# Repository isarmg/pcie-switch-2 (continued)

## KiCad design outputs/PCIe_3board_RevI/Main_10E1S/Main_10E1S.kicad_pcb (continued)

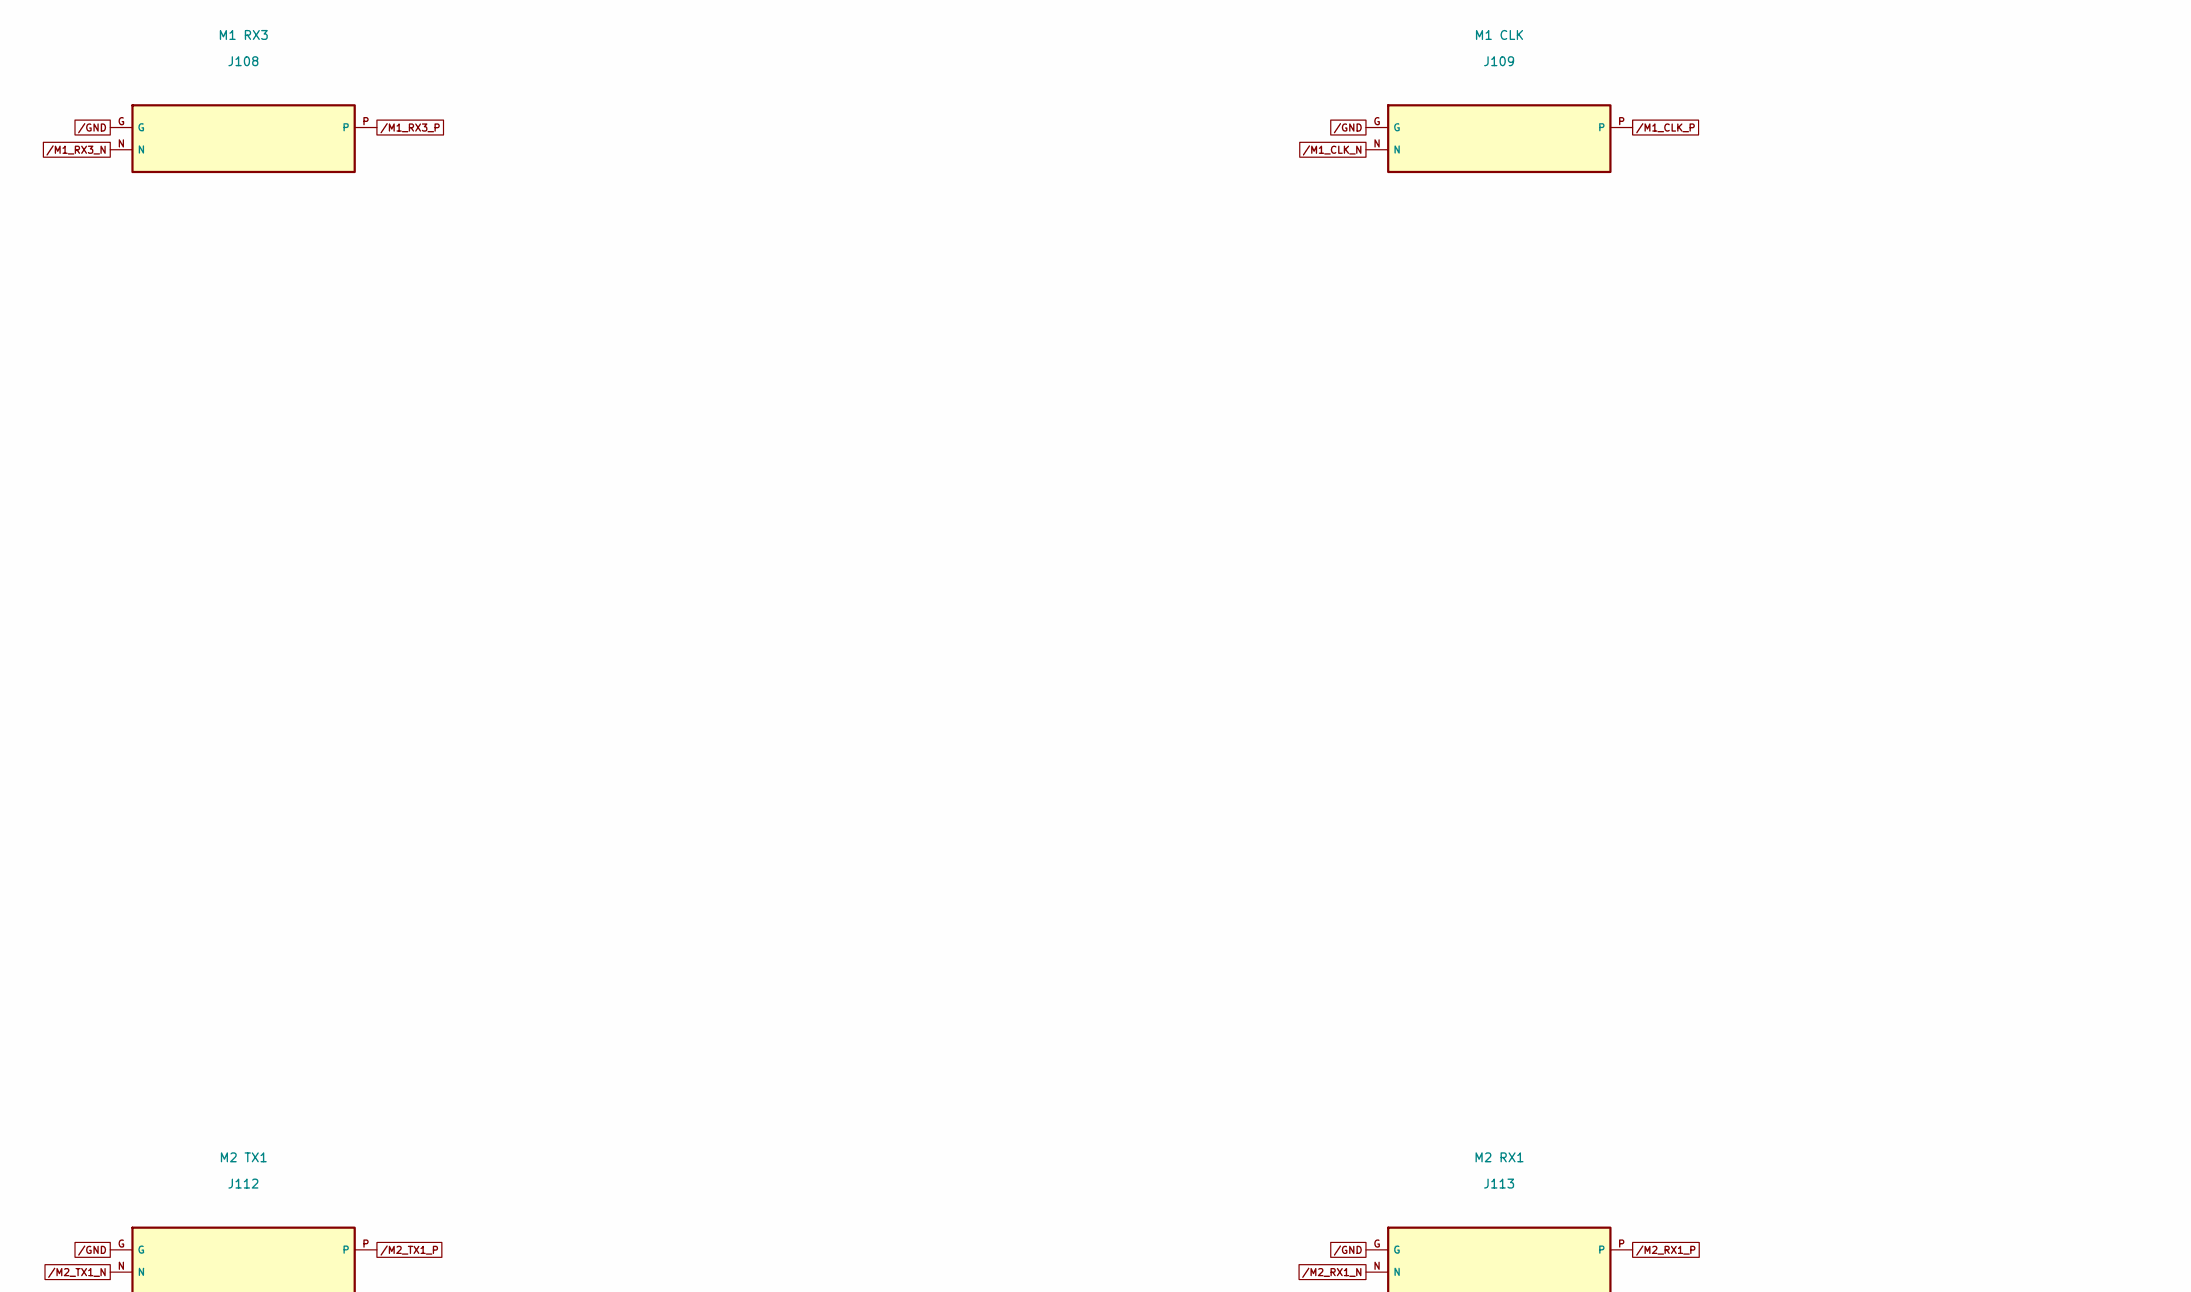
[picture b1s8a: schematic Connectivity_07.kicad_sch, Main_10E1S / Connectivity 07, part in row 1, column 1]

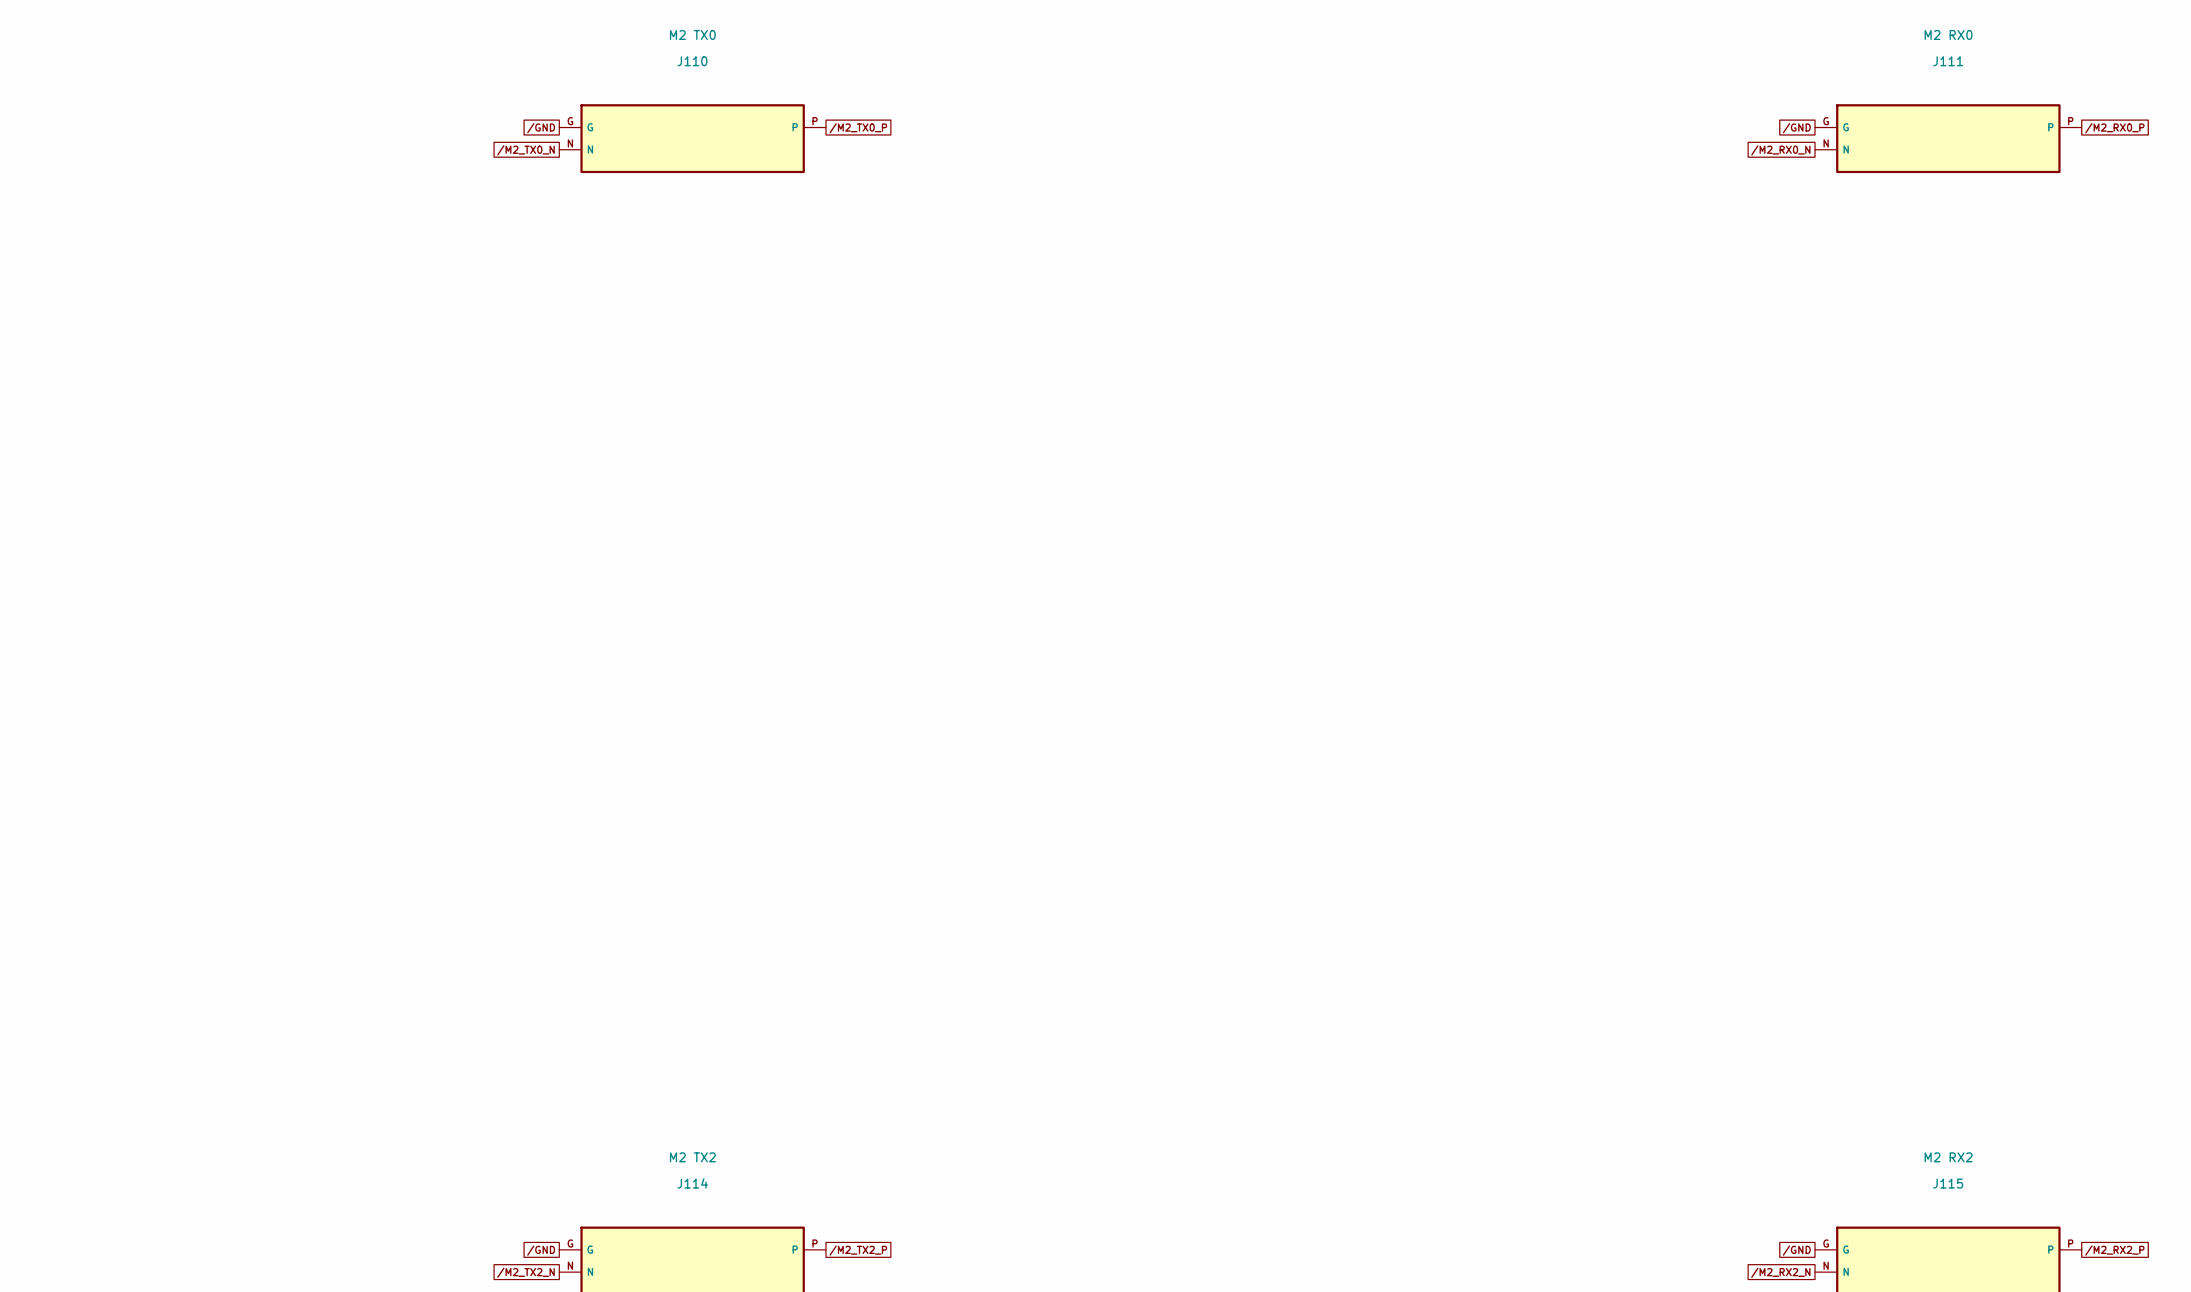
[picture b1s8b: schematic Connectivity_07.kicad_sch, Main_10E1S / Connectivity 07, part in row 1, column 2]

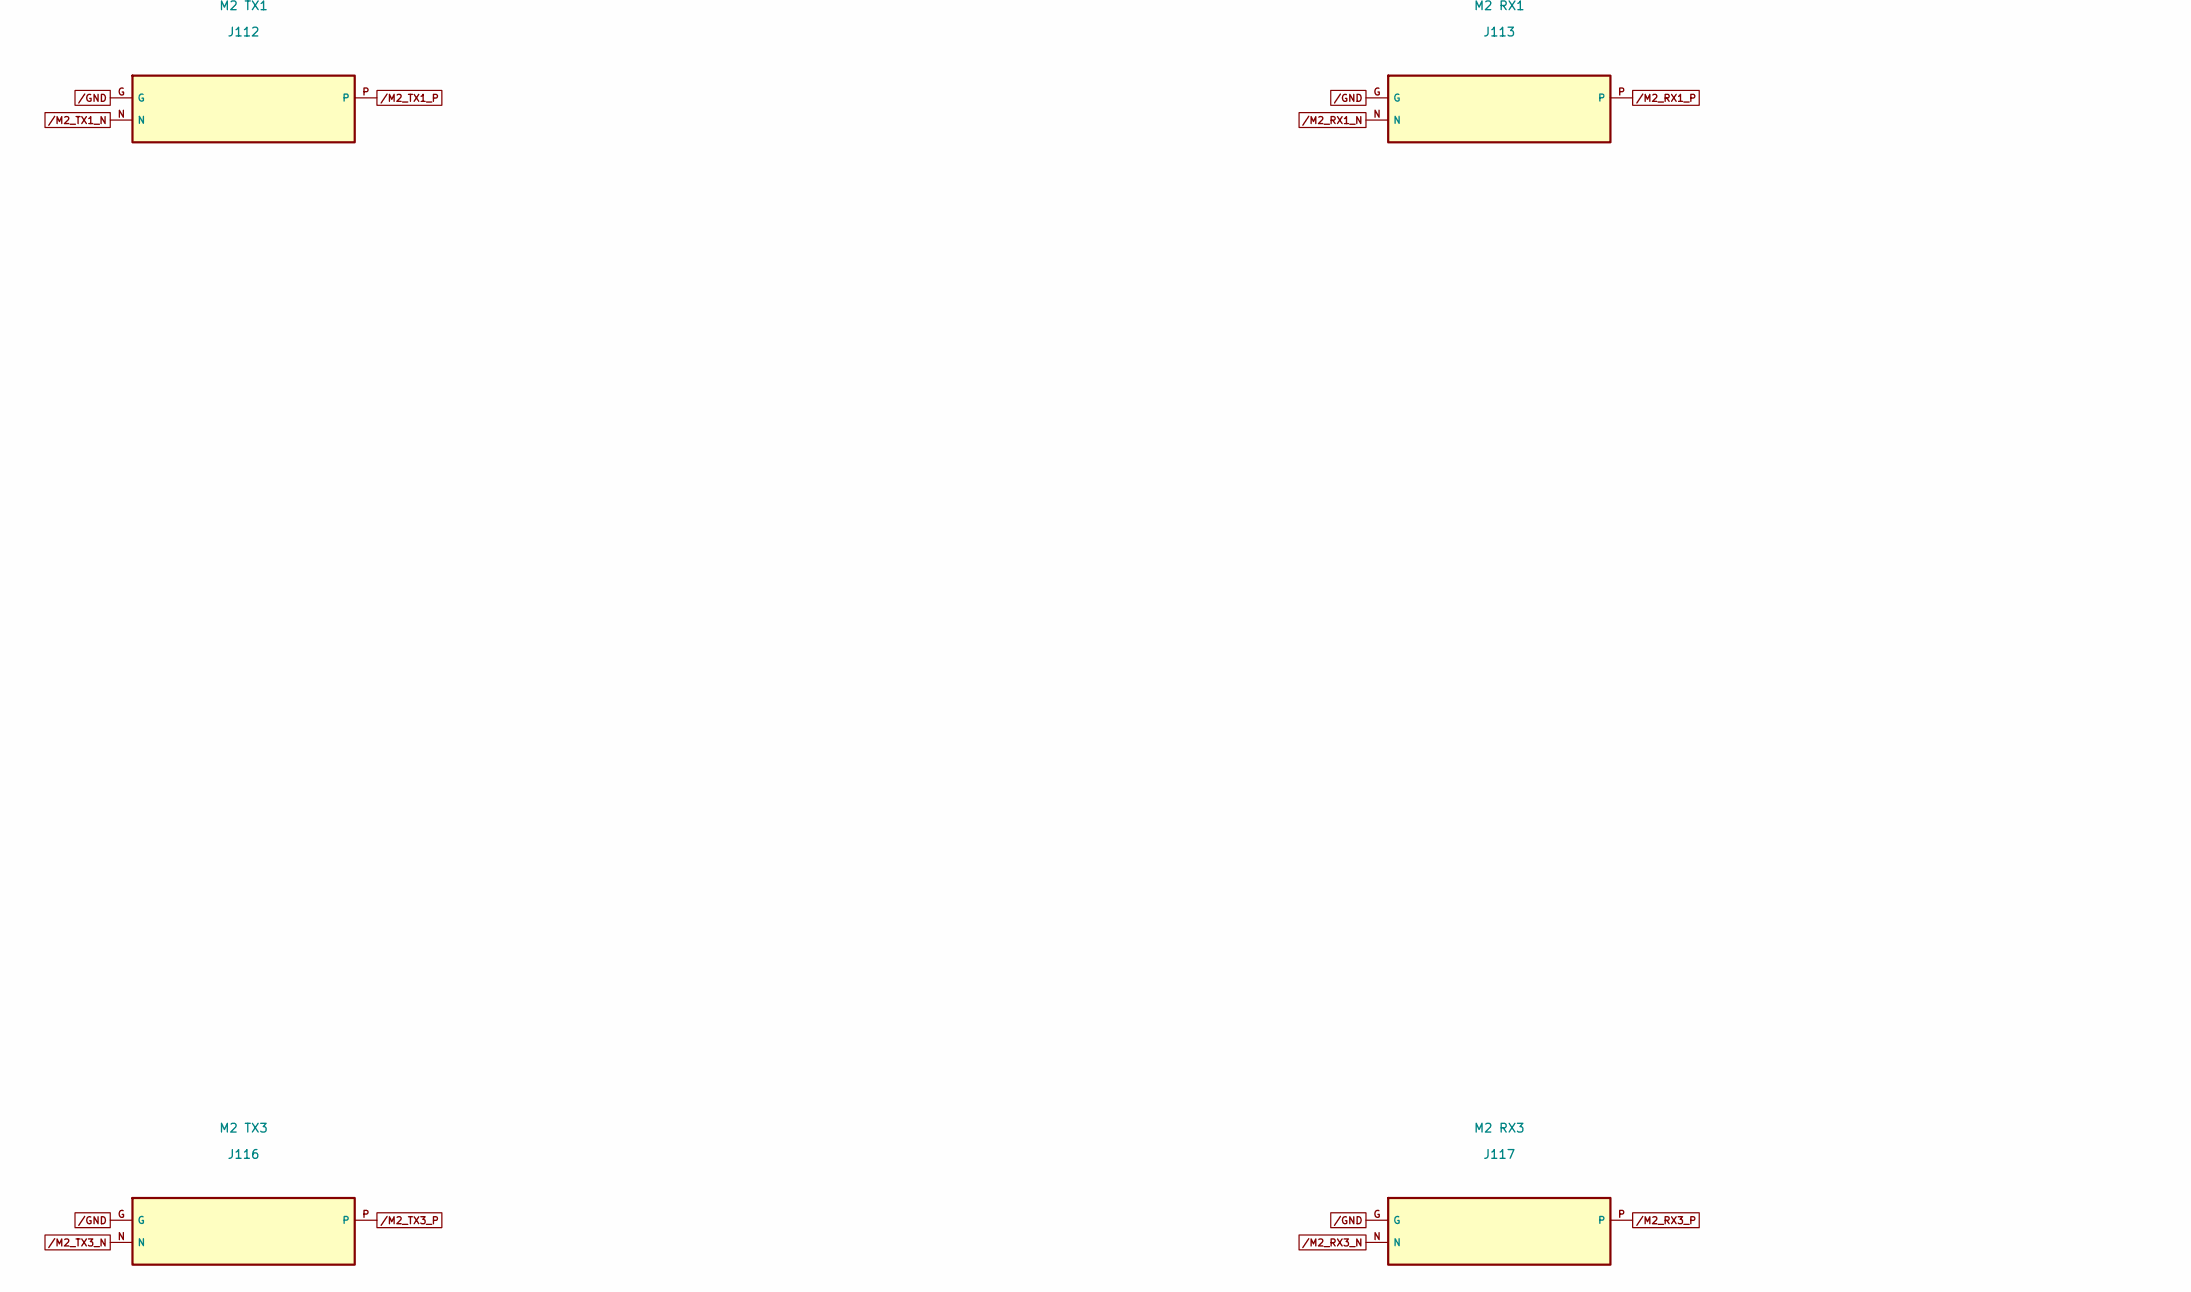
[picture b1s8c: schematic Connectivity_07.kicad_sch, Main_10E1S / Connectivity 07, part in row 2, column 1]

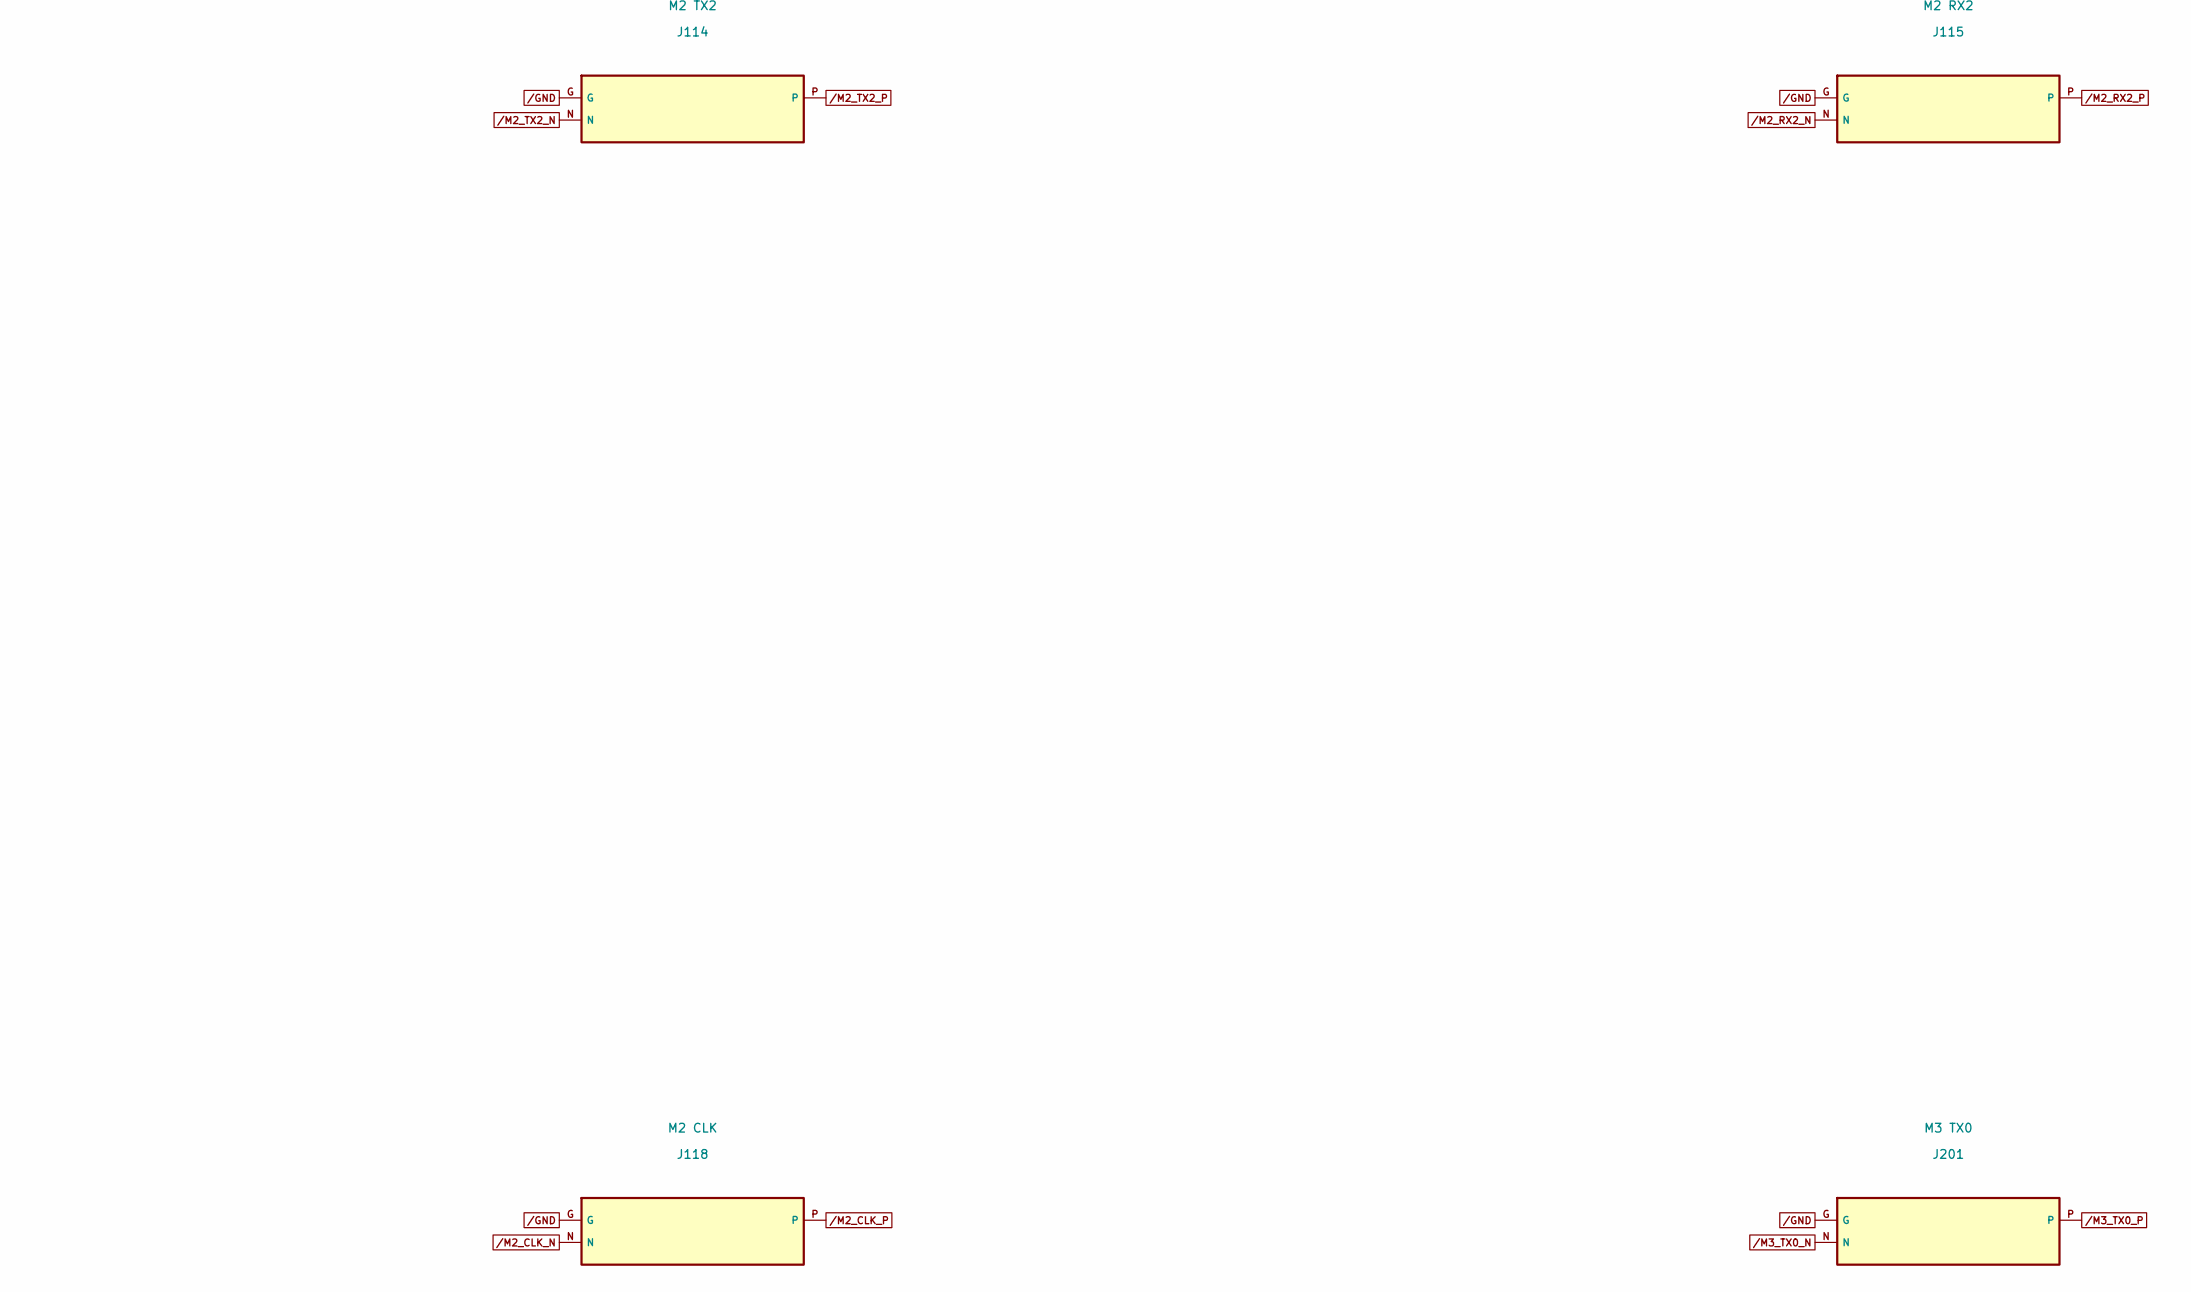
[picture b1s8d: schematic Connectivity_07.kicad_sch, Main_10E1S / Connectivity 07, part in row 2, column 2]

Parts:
J108: M1 RX3; Twinax_85R_Solder_DRAFT
J109: M1 CLK; Twinax_85R_Solder_DRAFT
J110: M2 TX0; Twinax_85R_Solder_DRAFT
J111: M2 RX0; Twinax_85R_Solder_DRAFT
J112: M2 TX1; Twinax_85R_Solder_DRAFT
J113: M2 RX1; Twinax_85R_Solder_DRAFT
J114: M2 TX2; Twinax_85R_Solder_DRAFT
J115: M2 RX2; Twinax_85R_Solder_DRAFT
J116: M2 TX3; Twinax_85R_Solder_DRAFT
J117: M2 RX3; Twinax_85R_Solder_DRAFT
J118: M2 CLK; Twinax_85R_Solder_DRAFT
J201: M3 TX0; Twinax_85R_Solder_DRAFT

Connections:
/GND: J108.G, J109.G, J110.G, J111.G, J112.G, J113.G, J114.G, J115.G, J116.G, J117.G, J118.G, J201.G; also elsewhere on the board
/M1_CLK_N: J109.N; also elsewhere on the board
/M1_CLK_P: J109.P; also elsewhere on the board
/M1_RX3_N: J108.N; also elsewhere on the board
/M1_RX3_P: J108.P; also elsewhere on the board
/M2_CLK_N: J118.N; also elsewhere on the board
/M2_CLK_P: J118.P; also elsewhere on the board
/M2_RX0_N: J111.N; also elsewhere on the board
/M2_RX0_P: J111.P; also elsewhere on the board
/M2_RX1_N: J113.N; also elsewhere on the board
/M2_RX1_P: J113.P; also elsewhere on the board
/M2_RX2_N: J115.N; also elsewhere on the board
/M2_RX2_P: J115.P; also elsewhere on the board
/M2_RX3_N: J117.N; also elsewhere on the board
/M2_RX3_P: J117.P; also elsewhere on the board
/M2_TX0_N: J110.N; also elsewhere on the board
/M2_TX0_P: J110.P; also elsewhere on the board
/M2_TX1_N: J112.N; also elsewhere on the board
/M2_TX1_P: J112.P; also elsewhere on the board
/M2_TX2_N: J114.N; also elsewhere on the board
/M2_TX2_P: J114.P; also elsewhere on the board
/M2_TX3_N: J116.N; also elsewhere on the board
/M2_TX3_P: J116.P; also elsewhere on the board
/M3_TX0_N: J201.N; also elsewhere on the board
/M3_TX0_P: J201.P; also elsewhere on the board

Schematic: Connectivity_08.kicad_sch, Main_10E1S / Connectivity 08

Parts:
J202: M3 RX0; Twinax_85R_Solder_DRAFT
J203: M3 TX1; Twinax_85R_Solder_DRAFT
J204: M3 RX1; Twinax_85R_Solder_DRAFT
J205: M3 TX2; Twinax_85R_Solder_DRAFT
J206: M3 RX2; Twinax_85R_Solder_DRAFT
J207: M3 TX3; Twinax_85R_Solder_DRAFT
J208: M3 RX3; Twinax_85R_Solder_DRAFT
J209: M3 CLK; Twinax_85R_Solder_DRAFT
J210: UP TX0; Twinax_85R_Solder_DRAFT
J211: UP RX0; Twinax_85R_Solder_DRAFT
J212: UP TX1; Twinax_85R_Solder_DRAFT
J213: UP RX1; Twinax_85R_Solder_DRAFT

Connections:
/GND: J202.G, J203.G, J204.G, J205.G, J206.G, J207.G, J208.G, J209.G, J210.G, J211.G, J212.G, J213.G; also elsewhere on the board
/M3_CLK_N: J209.N; also elsewhere on the board
/M3_CLK_P: J209.P; also elsewhere on the board
/M3_RX0_N: J202.N; also elsewhere on the board
/M3_RX0_P: J202.P; also elsewhere on the board
/M3_RX1_N: J204.N; also elsewhere on the board
/M3_RX1_P: J204.P; also elsewhere on the board
/M3_RX2_N: J206.N; also elsewhere on the board
/M3_RX2_P: J206.P; also elsewhere on the board
/M3_RX3_N: J208.N; also elsewhere on the board
/M3_RX3_P: J208.P; also elsewhere on the board
/M3_TX1_N: J203.N; also elsewhere on the board
/M3_TX1_P: J203.P; also elsewhere on the board
/M3_TX2_N: J205.N; also elsewhere on the board
/M3_TX2_P: J205.P; also elsewhere on the board
/M3_TX3_N: J207.N; also elsewhere on the board
/M3_TX3_P: J207.P; also elsewhere on the board
/UP_RX0_N: J211.N; also elsewhere on the board
/UP_RX0_P: J211.P; also elsewhere on the board
/UP_RX1_N: J213.N; also elsewhere on the board
/UP_RX1_P: J213.P; also elsewhere on the board
/UP_TX0_N: J210.N; also elsewhere on the board
/UP_TX0_P: J210.P; also elsewhere on the board
/UP_TX1_N: J212.N; also elsewhere on the board
/UP_TX1_P: J212.P; also elsewhere on the board

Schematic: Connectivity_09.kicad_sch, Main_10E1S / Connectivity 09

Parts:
J214: UP TX2; Twinax_85R_Solder_DRAFT
J215: UP RX2; Twinax_85R_Solder_DRAFT
J216: UP TX3; Twinax_85R_Solder_DRAFT
J217: UP RX3; Twinax_85R_Solder_DRAFT
J218: UP CLK; Twinax_85R_Solder_DRAFT
J301, J302: 12V protected / GND; Wire_12V_GND_3A
J303: L control / custom; Control_8_Wire
J304: R control / custom; Control_8_Wire
L31: 2.2uH; L_Coilcraft_XAL4020-XXX
R101: 76.1k; R_0402_1005Metric
R102: 10k; R_0402_1005Metric

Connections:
/BUCK_SW: L31.1; also elsewhere on the board
/CABLE12_L: J301.1; also elsewhere on the board
/CABLE12_R: J302.1; also elsewhere on the board
/GND: J214.G, J215.G, J216.G, J217.G, J218.G, J301.2, J302.2, J303.7, J303.8, J304.7, J304.8, R102.2; also elsewhere on the board
/M1_CLKREQ: J303.2; also elsewhere on the board
/M1_PERST: J303.1; also elsewhere on the board
/M1_WAKE: J303.3; also elsewhere on the board
/M2_CLKREQ: J303.5; also elsewhere on the board
/M2_PERST: J303.4; also elsewhere on the board
/M2_WAKE: J303.6; also elsewhere on the board
/M3_CLKREQ: J304.2; also elsewhere on the board
/M3_PERST: J304.1; also elsewhere on the board
/M3_WAKE: J304.3; also elsewhere on the board
/P3V3_AUX: L31.2; also elsewhere on the board
/S01_PWR_UV: R101.2, R102.1; also elsewhere on the board
/UP_CLKREQ: J304.5; also elsewhere on the board
/UP_CLK_N: J218.N; also elsewhere on the board
/UP_CLK_P: J218.P; also elsewhere on the board
/UP_PERST: J304.4; also elsewhere on the board
/UP_RX2_N: J215.N; also elsewhere on the board
/UP_RX2_P: J215.P; also elsewhere on the board
/UP_RX3_N: J217.N; also elsewhere on the board
/UP_RX3_P: J217.P; also elsewhere on the board
/UP_TX2_N: J214.N; also elsewhere on the board
/UP_TX2_P: J214.P; also elsewhere on the board
/UP_TX3_N: J216.N; also elsewhere on the board
/UP_TX3_P: J216.P; also elsewhere on the board
/UP_WAKE: J304.6; also elsewhere on the board
/VBANK_A: R101.1; also elsewhere on the board

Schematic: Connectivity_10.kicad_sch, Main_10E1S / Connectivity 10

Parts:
R103, R108, R113: 102k; R_0402_1005Metric
R104, R107, R109, R112, R114: 10k; R_0402_1005Metric
R105, R110: 1.10k; R_0402_1005Metric
R106, R111: 76.1k; R_0402_1005Metric

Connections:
/GND: R104.2, R105.2, R107.2, R109.2, R110.2, R112.2, R114.2; also elsewhere on the board
/S01_PWR_ILM: R105.1; also elsewhere on the board
/S01_PWR_OV: R103.2, R104.1; also elsewhere on the board
/S02_PWR_ILM: R110.1; also elsewhere on the board
/S02_PWR_OV: R108.2, R109.1; also elsewhere on the board
/S02_PWR_UV: R106.2, R107.1; also elsewhere on the board
/S03_PWR_OV: R113.2, R114.1; also elsewhere on the board
/S03_PWR_UV: R111.2, R112.1; also elsewhere on the board
/VBANK_A: R103.1, R106.1, R108.1, R111.1, R113.1; also elsewhere on the board

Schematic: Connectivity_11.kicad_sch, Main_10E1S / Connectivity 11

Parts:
R115, R120, R125: 1.10k; R_0402_1005Metric
R116, R121, R126: 76.1k; R_0402_1005Metric
R117, R119, R122, R124: 10k; R_0402_1005Metric
R118, R123: 102k; R_0402_1005Metric

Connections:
/GND: R115.2, R117.2, R119.2, R120.2, R122.2, R124.2, R125.2; also elsewhere on the board
/S03_PWR_ILM: R115.1; also elsewhere on the board
/S04_PWR_ILM: R120.1; also elsewhere on the board
/S04_PWR_OV: R118.2, R119.1; also elsewhere on the board
/S04_PWR_UV: R116.2, R117.1; also elsewhere on the board
/S05_PWR_ILM: R125.1; also elsewhere on the board
/S05_PWR_OV: R123.2, R124.1; also elsewhere on the board
/S05_PWR_UV: R121.2, R122.1; also elsewhere on the board
/S06_PWR_UV: R126.2; also elsewhere on the board
/VBANK_A: R116.1, R118.1, R121.1, R123.1; also elsewhere on the board
/VBANK_B: R126.1; also elsewhere on the board

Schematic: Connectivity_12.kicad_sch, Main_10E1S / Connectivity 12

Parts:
R127, R129, R132, R134, R137: 10k; R_0402_1005Metric
R128, R133, R138: 102k; R_0402_1005Metric
R130, R135: 1.10k; R_0402_1005Metric
R131, R136: 76.1k; R_0402_1005Metric

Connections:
/GND: R127.2, R129.2, R130.2, R132.2, R134.2, R135.2, R137.2; also elsewhere on the board
/S06_PWR_ILM: R130.1; also elsewhere on the board
/S06_PWR_OV: R128.2, R129.1; also elsewhere on the board
/S06_PWR_UV: R127.1; also elsewhere on the board
/S07_PWR_ILM: R135.1; also elsewhere on the board
/S07_PWR_OV: R133.2, R134.1; also elsewhere on the board
/S07_PWR_UV: R131.2, R132.1; also elsewhere on the board
/S08_PWR_OV: R138.2; also elsewhere on the board
/S08_PWR_UV: R136.2, R137.1; also elsewhere on the board
/VBANK_B: R128.1, R131.1, R133.1, R136.1, R138.1; also elsewhere on the board

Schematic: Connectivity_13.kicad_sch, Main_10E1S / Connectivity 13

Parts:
R139, R142, R144, R147, R149: 10k; R_0402_1005Metric
R140, R145, R150: 1.10k; R_0402_1005Metric
R141, R146: 76.1k; R_0402_1005Metric
R143, R148: 102k; R_0402_1005Metric

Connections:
/GND: R139.2, R140.2, R142.2, R144.2, R145.2, R147.2, R149.2, R150.2; also elsewhere on the board
/S08_PWR_ILM: R140.1; also elsewhere on the board
/S08_PWR_OV: R139.1; also elsewhere on the board
/S09_PWR_ILM: R145.1; also elsewhere on the board
/S09_PWR_OV: R143.2, R144.1; also elsewhere on the board
/S09_PWR_UV: R141.2, R142.1; also elsewhere on the board
/S10_PWR_ILM: R150.1; also elsewhere on the board
/S10_PWR_OV: R148.2, R149.1; also elsewhere on the board
/S10_PWR_UV: R146.2, R147.1; also elsewhere on the board
/VBANK_B: R141.1, R143.1, R146.1, R148.1; also elsewhere on the board

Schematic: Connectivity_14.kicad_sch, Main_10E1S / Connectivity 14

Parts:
R301, R411, R421: 76.1k; R_0402_1005Metric
R302, R304, R412, R414: 10k; R_0402_1005Metric
R303, R413: 102k; R_0402_1005Metric
R305: 3.32k; R_0402_1005Metric
R311: 100k; R_0402_1005Metric
R415: 1.10k; R_0402_1005Metric

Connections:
/AUX_ILM: R305.1; also elsewhere on the board
/AUX_OV: R303.2, R304.1; also elsewhere on the board
/AUX_PG: R311.2; also elsewhere on the board
/AUX_UV: R301.2, R302.1; also elsewhere on the board
/EXT_41_ILM: R415.1; also elsewhere on the board
/EXT_41_OV: R413.2, R414.1; also elsewhere on the board
/EXT_41_UV: R411.2, R412.1; also elsewhere on the board
/EXT_42_UV: R421.2; also elsewhere on the board
/GND: R302.2, R304.2, R305.2, R412.2, R414.2, R415.2; also elsewhere on the board
/P3V3_AUX: R311.1; also elsewhere on the board
/VBANK_A: R301.1, R303.1; also elsewhere on the board
/VIN_A: R411.1, R413.1; also elsewhere on the board
/VIN_B: R421.1; also elsewhere on the board

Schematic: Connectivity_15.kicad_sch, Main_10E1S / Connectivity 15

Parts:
R422, R424: 10k; R_0402_1005Metric
R423: 102k; R_0402_1005Metric
R425: 1.10k; R_0402_1005Metric
U11, U12, U13, U14, U15, U16, U17, U18: TPS259470ARPWR; TI_RPW0010A_TPS25947

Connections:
/EXT_42_ILM: R425.1; also elsewhere on the board
/EXT_42_OV: R423.2, R424.1; also elsewhere on the board
/EXT_42_UV: R422.1; also elsewhere on the board
/GND: R422.2, R424.2, R425.2, U11.8, U12.8, U13.8, U14.8, U15.8, U16.8, U17.8, U18.8; also elsewhere on the board
/P12_SLOT01: U11.6; also elsewhere on the board
/P12_SLOT02: U12.6; also elsewhere on the board
/P12_SLOT03: U13.6; also elsewhere on the board
/P12_SLOT04: U14.6; also elsewhere on the board
/P12_SLOT05: U15.6; also elsewhere on the board
/P12_SLOT06: U16.6; also elsewhere on the board
/P12_SLOT07: U17.6; also elsewhere on the board
/P12_SLOT08: U18.6; also elsewhere on the board
/S01_PWR_DVDT: U11.7; also elsewhere on the board
/S01_PWR_ILM: U11.9; also elsewhere on the board
/S01_PWR_OV: U11.2; also elsewhere on the board
/S01_PWR_UV: U11.1; also elsewhere on the board
/S02_PWR_DVDT: U12.7; also elsewhere on the board
/S02_PWR_ILM: U12.9; also elsewhere on the board
/S02_PWR_OV: U12.2; also elsewhere on the board
/S02_PWR_UV: U12.1; also elsewhere on the board
/S03_PWR_DVDT: U13.7; also elsewhere on the board
/S03_PWR_ILM: U13.9; also elsewhere on the board
/S03_PWR_OV: U13.2; also elsewhere on the board
/S03_PWR_UV: U13.1; also elsewhere on the board
/S04_PWR_DVDT: U14.7; also elsewhere on the board
/S04_PWR_ILM: U14.9; also elsewhere on the board
/S04_PWR_OV: U14.2; also elsewhere on the board
/S04_PWR_UV: U14.1; also elsewhere on the board
/S05_PWR_DVDT: U15.7; also elsewhere on the board
/S05_PWR_ILM: U15.9; also elsewhere on the board
/S05_PWR_OV: U15.2; also elsewhere on the board
/S05_PWR_UV: U15.1; also elsewhere on the board
/S06_PWR_DVDT: U16.7; also elsewhere on the board
/S06_PWR_ILM: U16.9; also elsewhere on the board
/S06_PWR_OV: U16.2; also elsewhere on the board
/S06_PWR_UV: U16.1; also elsewhere on the board
/S07_PWR_DVDT: U17.7; also elsewhere on the board
/S07_PWR_ILM: U17.9; also elsewhere on the board
/S07_PWR_OV: U17.2; also elsewhere on the board
/S07_PWR_UV: U17.1; also elsewhere on the board
/S08_PWR_DVDT: U18.7; also elsewhere on the board
/S08_PWR_ILM: U18.9; also elsewhere on the board
/S08_PWR_OV: U18.2; also elsewhere on the board
/S08_PWR_UV: U18.1; also elsewhere on the board
/VBANK_A: U11.5, U12.5, U13.5, U14.5, U15.5; also elsewhere on the board
/VBANK_B: U16.5, U17.5, U18.5; also elsewhere on the board
/VIN_B: R423.1; also elsewhere on the board

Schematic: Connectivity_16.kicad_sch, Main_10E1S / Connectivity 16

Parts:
U19, U20, U30, U41, U42: TPS259470ARPWR; TI_RPW0010A_TPS25947
U31: TPS62132RGTR; VQFN-16-1EP_3x3mm_P0.5mm_EP1.68x1.68mm

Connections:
/AUX_12V_PROTECTED: U30.6, U31.10, U31.11, U31.12, U31.13; also elsewhere on the board
/AUX_DVDT: U30.7; also elsewhere on the board
/AUX_ILM: U30.9; also elsewhere on the board
/AUX_OV: U30.2; also elsewhere on the board
/AUX_PG: U31.4; also elsewhere on the board
/AUX_UV: U30.1; also elsewhere on the board
/BUCK_SS: U31.9; also elsewhere on the board
/BUCK_SW: U31.1, U31.2, U31.3; also elsewhere on the board
/CABLE12_L: U41.6; also elsewhere on the board
/CABLE12_R: U42.6; also elsewhere on the board
/EXT_41_DVDT: U41.7; also elsewhere on the board
/EXT_41_ILM: U41.9; also elsewhere on the board
/EXT_41_OV: U41.2; also elsewhere on the board
/EXT_41_UV: U41.1; also elsewhere on the board
/EXT_42_DVDT: U42.7; also elsewhere on the board
/EXT_42_ILM: U42.9; also elsewhere on the board
/EXT_42_OV: U42.2; also elsewhere on the board
/EXT_42_UV: U42.1; also elsewhere on the board
/GND: U19.8, U20.8, U30.8, U31.5, U31.6, U31.7, U31.8, U31.15, U31.16, U31.17, U41.8, U42.8; also elsewhere on the board
/P3V3_AUX: U31.14; also elsewhere on the board
/P12_SLOT09: U19.6; also elsewhere on the board
/P12_SLOT10: U20.6; also elsewhere on the board
/S09_PWR_DVDT: U19.7; also elsewhere on the board
/S09_PWR_ILM: U19.9; also elsewhere on the board
/S09_PWR_OV: U19.2; also elsewhere on the board
/S09_PWR_UV: U19.1; also elsewhere on the board
/S10_PWR_DVDT: U20.7; also elsewhere on the board
/S10_PWR_ILM: U20.9; also elsewhere on the board
/S10_PWR_OV: U20.2; also elsewhere on the board
/S10_PWR_UV: U20.1; also elsewhere on the board
/VBANK_A: U30.5; also elsewhere on the board
/VBANK_B: U19.5, U20.5; also elsewhere on the board
/VIN_A: U41.5; also elsewhere on the board
/VIN_B: U42.5; also elsewhere on the board

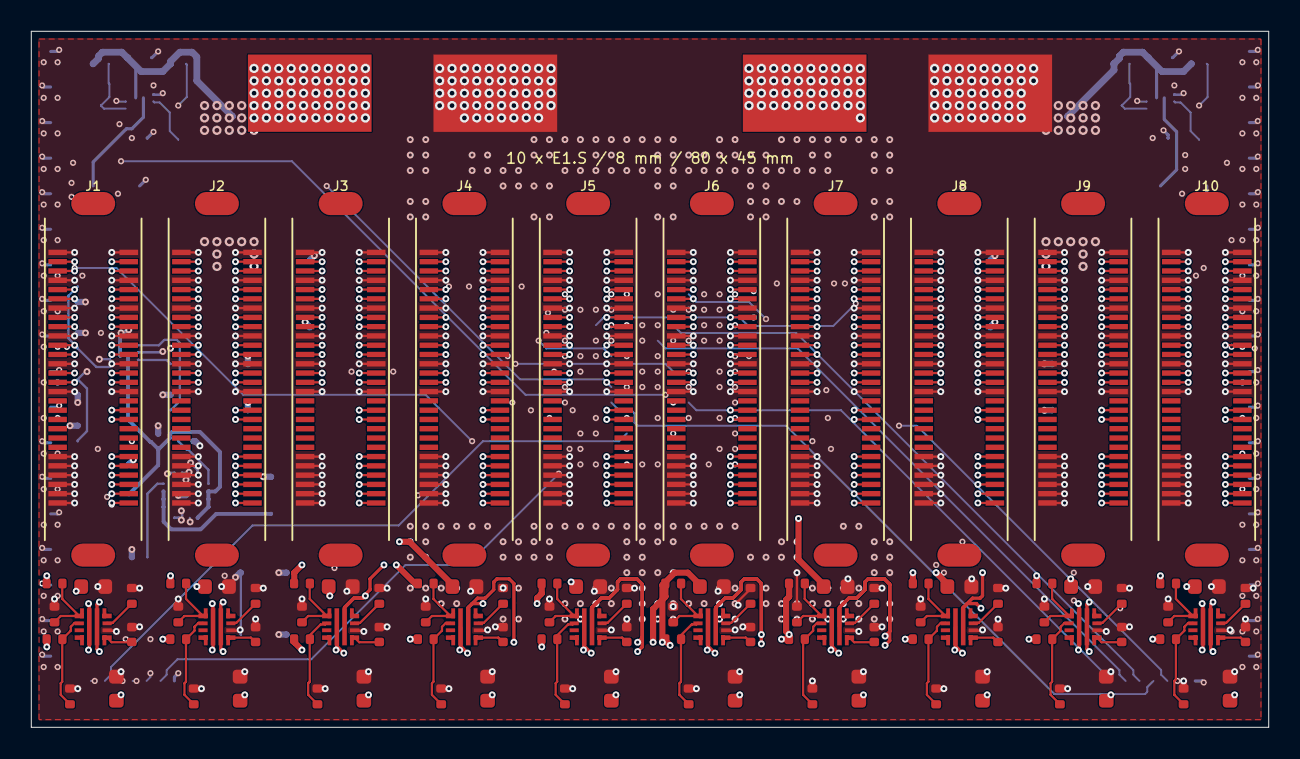
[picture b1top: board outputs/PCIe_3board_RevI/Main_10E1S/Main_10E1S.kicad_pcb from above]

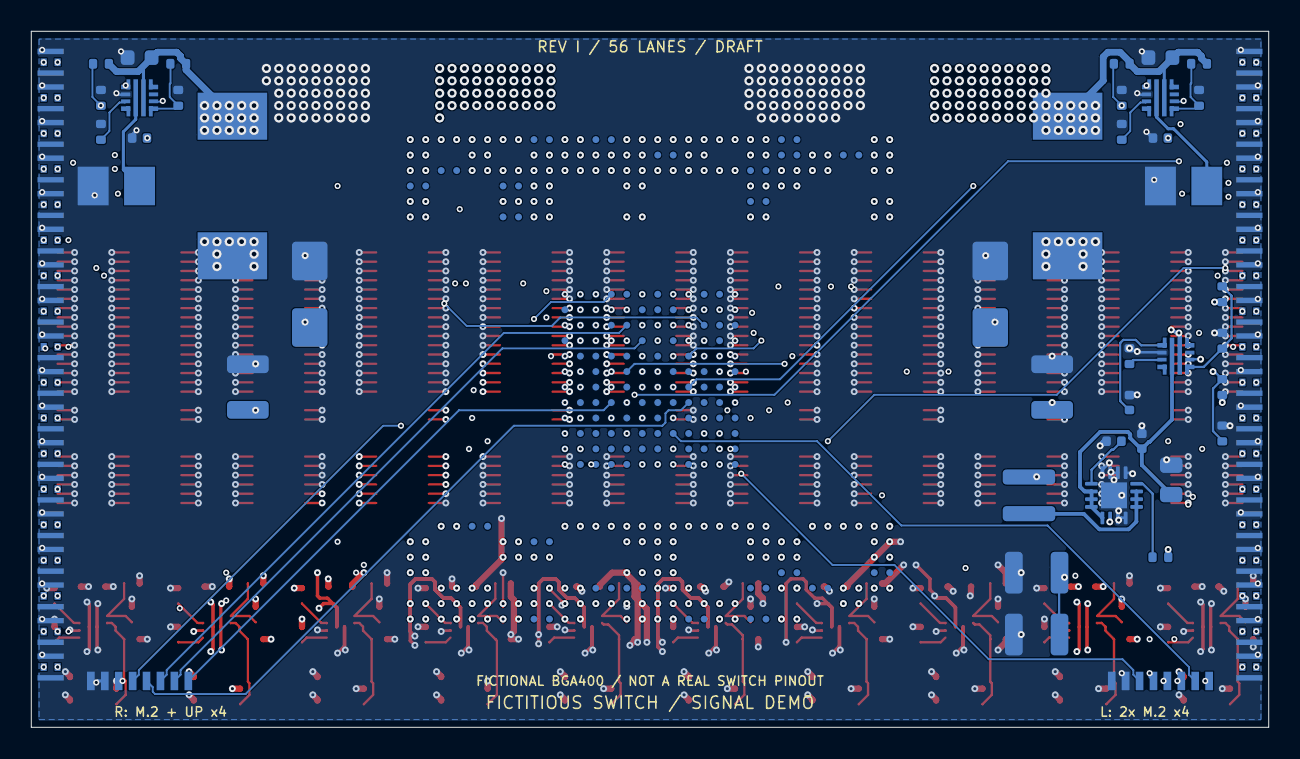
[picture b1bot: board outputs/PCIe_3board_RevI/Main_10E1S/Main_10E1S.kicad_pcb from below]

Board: 32 copper layers, 80.0 x 45.0 mm, 180 parts (78 on the bottom side), 368 nets.

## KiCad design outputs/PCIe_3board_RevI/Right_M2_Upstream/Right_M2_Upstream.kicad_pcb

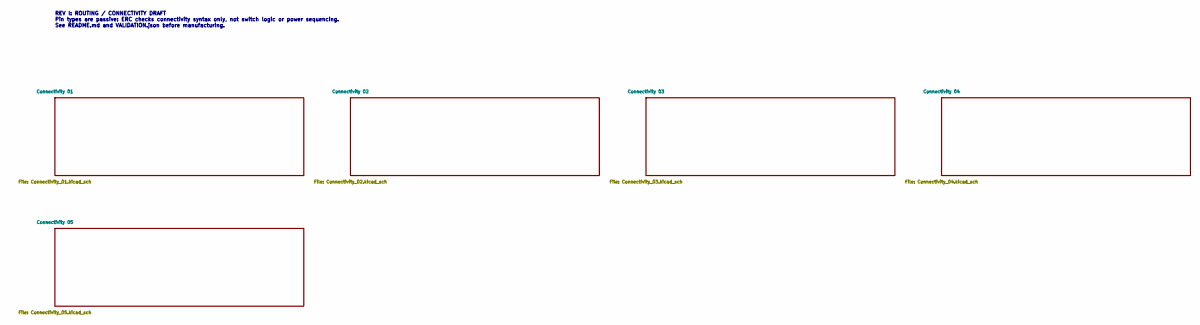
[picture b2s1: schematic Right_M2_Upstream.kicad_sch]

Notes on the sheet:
REV I: ROUTING / CONNECTIVITY DRAFT Pin types are passive: ERC checks connectivity syntax only, not switch logic or power sequencing. See README.md and VALIDATION.json before manufacturing.
